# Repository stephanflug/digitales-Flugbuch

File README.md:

<div align="center" width="100%">
    
</div>

# Digitales Flugbuch für Modellflug Vereine

Mit der Software und der Verbindung zu einem Raspberry Pi Zero kann eine digitale Aufzeichnung erstellt werden, die den Anforderungen der aktuellen Verordnung (EU) 2019/947 entspricht.Für Österreich und Deutschland(kann man unter Einstellungen festlegen)

## Kontakt  
Bei Fragen können Sie mich gerne per E-Mail erreichen:  
📧 [steuerung@gmx.at](mailto:steuerung@gmx.at)
oder auch auf dieser Seite [Flugbuch](https://flugbuch.gltdienst.home64.de))

## ⭐ Features

- 🧑‍💼 RFID-Erkennung und Nutzerverifizierung: Wenn ein Benutzer seinen RFID-Chip auf das Lesegerät legt, wird die aktuelle Uhrzeit    zusammen mit dem Namen des Benutzers aus der Benutzerdatei gespeichert. 
- ⌨️ Falls der Benutzer nicht in der Benutzerdatei existiert, wird eine Fehlermeldung ausgegeben.

## ⭐ NEU!

### 🖥️ Flugbuch Cloud Server Panel (Windows) – ab Version 3.9.0

Mit Version **v3.9.0** steht ein neues **Flugbuch Cloud Server Panel für Windows** zur Verfügung.  
Das Panel läuft lokal auf einem Windows-Rechner (z. B. im Vereinsheim) und verbindet sich automatisch mit dem Vereinsflugbuch in der Flugbuch Cloud. Der volle Funktionsumfang des Flugbuchs steht direkt zur Verfügung.

👉 Release-Details:  
https://github.com/stephanflug/digitales-Flugbuch/releases

---

### 🔎 RFID Chip Scanner (Windows & Android)

Zusätzlich zum Flugbuch stehen einfache Hilfstools zum Auslesen der UID von RFID-/NFC-Chips zur Verfügung:

- 🖥️ Windows-Tool für USB-RFID-Lesegeräte  
- 📱 Android-App für NFC-fähige Smartphones  

Die Tools lesen ausschließlich die UID des Chips aus, zeigen sie direkt an und arbeiten vollständig eigenständig.  
Die UID kann im Flugbuch zur eindeutigen Zuordnung von Nutzerchips verwendet werden.

👉 [Zum RFID Chip Scanner](./Tool%20Software/RFID%20Chip%20Scanner/README.md)

---

### 💾 Flugbuch Basic Image

Ein fertiges **Flugbuch Basic Image** steht zum Download bereit.  
Einfach herunterladen und auf die SD-Karte speichern.  
**Bitte unbedingt die Installationsanleitung beachten.**

👉 [Installationsanleitung (PDF)](https://github.com/stephanflug/digitales-Flugbuch/tree/main/Dokumentation/Installation/Flugbuch%20Images)
👉 [Flugbuch Basic Image herunterladen](https://github.com/stephanflug/digitales-Flugbuch/releases)
---

### 📈 Altitude Sensor (ab Version 3.5)

Ab Version **3.5** steht die **Altitude-Sensor-Funktion** zur Verfügung.

👉 [Anleitung (PDF)](https://github.com/stephanflug/digitales-Flugbuch/blob/main/Dokumentation/FlugBuch/RFID%20Flugbuch/Altitude%20Sensor%20beim%20Flugbuch%20einbindenV1.0.pdf)  
👉 Altitude Sensor Projekt: https://github.com/stephanflug/AltitudeSensor

---

### 🧪 Aktuelle getestete Geräte

- ✅ **Pi Zero W2** – getestet  
- ✅ **Pi 3B** – getestet  
- 🔄 **Pi 4** – getestet  
- ⏳ **Pi 5** – getestet

## ⭐ Möglichkeiten:
    -Keinen Cloudzwang
    -Flugbuch-Auswertung direkt auf dem Gerät
    -Möglichkeit, das gesamte Flugbuch zu löschen
    -Flugbuch Einträge bearbeiten
    -Flugbuch-Ausgabe im JSON-Format
    -Flugbuch export in CSV
    -Systeminformationen anzeigen
    -Mail versand
    -Browser Zugang für die Verwaltung
    -Serviceebene direkt auf dem Gerät
    -MQTT
    -MFSD Schnitstelle
    -Kann auch ohne Internet betrieben werden(Nur wenn eine RTC Batterie verbaut wurde)
    -Backup und Restore
    -Viewer Dashboard für eine externen Anzeige via Browser
    -Rest-API Schnitstelle die Flugbuchdaten zu übermitteln
    -Ab der 3.5 Version ist es jetzt möglich einen Altitude Sensor zu verwenden.
    -Bossserver Funktionen.Eine externe Betriebsaufzeichnung auf dem Vereinsserver.
    -VPN Zugang direkt zum Gerät via Flugbuch Cloud Server oder Verein eigenen Server
    -Integration in Areoclub Flugbuch Online

## 🔧 Vorbereitung: 
```
Benötigte Hardware
- ✅ Raspberry Pi 3 oder höher oder Raspberry Pi 2 Zero. Vereine über 30 User sollten einen Pi 4 verwenden.
- ✅ Speicherkarte (microSD) Kapazität: Mindestens 16 GB, idealerweise 32 GB oder mehr.
- ✅ Ein stabiles und ausreichend starkes Netzteil.
- ✅ Ein Gehäuse 
- ✅ Einen Kühlkörper für den Prozessor.
- ✅ RFID-Modul MFRC522
- ✅ 16-Tasten-Keypad (4x4) mit I2c
- ✅ 1602 LCD-Display mit I2C-Modul
- ✅ RFID-Tags oder -Karten
- ✅ RTC Batterie für den offline Modus(nur wenn das Gerät kein Internet hat)
```
## 🚀 Schnellstart

Verwenden Sie das bereits vorbereitete Image – das spart Zeit und schont die Nerven.

👉 [**Installation: Betriebssystem auf SD-Karte**](https://github.com/stephanflug/digitales-Flugbuch/releases)
👉 [**Doko: Betriebssystem auf SD-Karte**](https://github.com/stephanflug/digitales-Flugbuch/blob/main/Dokumentation/Installation/Flugbuch%20Images/Anleitung_Flugbuch_Images.pdf)  

## 🛠️ Alternative Installation auf einem eigenen Raspberry Pi

Wenn Sie das fertige Image nicht verwenden möchten, können Sie die Software auch manuell auf einem selbst eingerichteten Raspberry Pi installieren.

### ✅ Voraussetzungen

- **Hardware:** Raspberry Pi Zero W2 (oder kompatibles Modell)
- **Betriebssystem:** Vorinstalliertes Linux auf der SD-Karte  
  - **Empfohlen:** Raspberry Pi OS Lite oder Raspberry Pi OS Desktop  
  - **Alternativen:** Ubuntu MATE, DietPi, Arch Linux (sofern kompatibel mit Raspberry Pi)
  -  Speichermedium (SD-Karte) Hochwertige SD-Karte (z. B. SanDisk High Endurance oder Samsung Pro Endurance).

### 📦 Vorbereitung

#### 1. Betriebssystem installieren

Falls noch kein Betriebssystem installiert ist:

- Laden Sie den [**Raspberry Pi Imager**](https://www.raspberrypi.com/software/) herunter.
- Wählen Sie ein geeignetes Linux-Betriebssystem (z. B. Raspberry Pi OS).
- Installieren Sie es auf die SD-Karte.

👉 Eine Schritt-für-Schritt-Anleitung finden Sie in der [offiziellen Raspberry Pi-Dokumentation](https://www.raspberrypi.com/documentation/computers/getting-started.html).

#### 2. Raspberry Pi einrichten

- SD-Karte in den Raspberry Pi einlegen
- Monitor, Tastatur und Maus anschließen
- Gerät starten und überprüfen, ob das System korrekt läuft
- Internetverbindung sicherstellen (WLAN oder Ethernet)

> ⚠️ **Hinweis:** Ohne ein vorinstalliertes Linux-Betriebssystem kann dieses Projekt nicht ausgeführt werden. Bitte stellen Sie sicher, dass das System korrekt installiert und betriebsbereit ist, bevor Sie fortfahren.

###
1. Vorbereitungen nur wenn Docker noch nicht auf dem System installiert wurde sonst weiter mit Postion 3
###  
Als Video ansehen:    <a href="https://github.com/stephanflug/digitales-Flugbuch/blob/main/Installation/Neuinstallation/Video/InstallationVideoFlugBuchsoftware.mp4" target="_blank">Video</a>

Aktualisiere das System:
```
sudo apt update
sudo apt upgrade -y
```

Die empfohlene Methode zur Installation von Docker auf einem Raspberry Pi ist die Verwendung des offiziellen Installationsskripts von Docker, das alle notwendigen Repositorys und Schritte berücksichtigt. 
```
curl -fsSL https://get.docker.com -o get-docker.sh
```
```
sudo sh get-docker.sh
```

2. Docker-Dienst aktivieren
```
sudo systemctl start docker
```
```
sudo systemctl enable docker
```
3.Verzeichniss erstellen für script
```
sudo mkdir -p /opt/digitalflugbuch
```
4.Wechsel dann in das Verzeichnis:
```
cd /opt/digitalflugbuch
```

5a. Herunterladen des Skripts mit wget mit Raspberry Pi 3/4/5 Zero 2W oder höher: Prozessor ARMV7
```
sudo wget -O script.sh https://raw.githubusercontent.com/stephanflug/digitales-Flugbuch/main/script_armv7.sh
```

6. Anmeldeung als root Benutzer wenn das Passwort noch nicht gesetzt wurde mit sudo passwd root
```
su
```

6. Script ausführen.
```
sudo bash script.sh
```
7.Raspi-Config aufrufen
```
sudo raspi-config
```
Menüoptionen von raspi-config
> Interface Options
>Aktivierung von Schnittstellen wie  I2C, SPI

8.Gerät neustarten
```
sudo reboot
```

Beispielablauf:
Das Skript wird heruntergeladen und im aktuellen Verzeichnis gespeichert.
Es wird ausführbar gemacht, sodass du es wie ein Programm starten kannst.
Schließlich wird das Skript ausgeführt, und es erledigt alle im Code definierten Aufgaben.

9. Status prüfen:
```
sudo docker ps
```

10. Danach können Sie die Verwaltungsseite öffnen.
```
Startseite url:http://<IPAdresse>:1880/home
```

11 Schaltplan Prinzipschema:   <a href="https://github.com/stephanflug/digitales-Flugbuch/blob/main/Schaltplan/BelegungsaufstellungV1.0.pdf" target="_blank">Belegungsaufstellung</a>

11a Version 1 mit RFID RC522 (alte Version. Empfehlung:Bei Neuinstallation Version 2 zu verwenden)

11b Version 1B mit RFID RC522 + RTC

11c Version 2 mit RFID PN532 + (RTC muss man nicht ausführen wenn das Gerät Internet Zugang hat)

12. Zugriff via Browser: Weitere Bilder Hier: <a href="https://github.com/stephanflug/digitales-Flugbuch/tree/main/Bilder/Webbedienung" target="_blank">Bilder</a>

13. Videos:

###
1.1 Neues Update einspielen

Hinweis: Wenn Sie bereits das fertige Image verwenden, müssen Sie lediglich die IP-Adresse des Geräts in den Browser eingeben. Sie gelangen dann direkt zur Grundkonfiguration, in der Sie im Menü den Punkt „Flugbuch-Update“ finden.
Diese Schritte sind in diesem Fall nicht mehr erforderlich.

1.2 Wechsel in das Verzeichnis:
```
cd /opt/digitalflugbuch
```
1.3 Herunterladen des Skripts
```
sudo wget -O update_script.sh https://raw.githubusercontent.com/stephanflug/digitales-Flugbuch/main/update_script_armv7.sh
```
1.4  Anmeldeung als root Benutzer
```
su
```

1.5. Script ausführen.
```
sudo bash update_script.sh
```
1.6.Gerät neustarten
```
sudo reboot
```

### ☕ Unterstütze das Büro-Kaffeekonto!

Damit der Kaffee im Büro nie ausgeht und die Entwicklung weiter auf Hochtouren läuft, freuen wir uns über eine kleine Unterstützung. ☕💻

Jeder Beitrag hilft dabei, die Kaffeemaschine am Laufen zu halten und sorgt für genügend Energie für neue Ideen, Funktionen und Updates.

**☕ [Kaffee via PayPal spendieren](https://paypal.me/stephanflug)**

Vielen Dank für deine Unterstützung! ❤️

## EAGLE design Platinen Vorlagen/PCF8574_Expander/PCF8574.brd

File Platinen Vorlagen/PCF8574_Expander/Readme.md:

Platinen-Layout ist mit "Eagle 7" gemacht , die e12 Datei im Isolationsfräsen mit "Estlcam 12"

von Manfred Stratmann

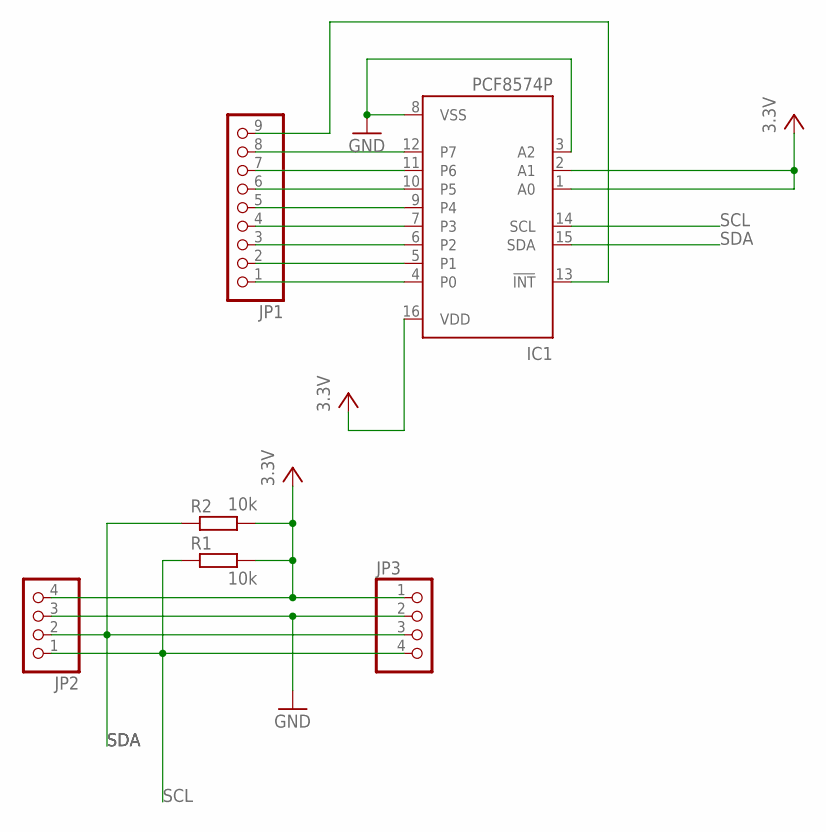
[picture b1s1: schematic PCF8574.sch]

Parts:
IC1: PCF8574P; DIL16
JP1: PINHD-1X9; 1X09
JP2, JP3: PINHD-1X4/90; 1X04/90
R1, R2: 10k; 0309/12

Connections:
GND: IC1.3 (A2), IC1.8 (VSS), JP2.3, JP3.2
unnamed: IC1.4 (P0), JP1.1
unnamed: IC1.5 (P1), JP1.2
unnamed: IC1.6 (P2), JP1.3
unnamed: IC1.7 (P3), JP1.4
unnamed: IC1.9 (P4), JP1.5
unnamed: IC1.10 (P5), JP1.6
unnamed: IC1.11 (P6), JP1.7
unnamed: IC1.12 (P7), JP1.8
unnamed: IC1.13 (!INT), JP1.9
SCL: IC1.14 (SCL), JP2.1, JP3.4, R1.1
SDA: IC1.15 (SDA), JP2.2, JP3.3, R2.1
VCC: IC1.1 (A0), IC1.2 (A1), IC1.16 (VDD), JP2.4, JP3.1, R1.2, R2.2

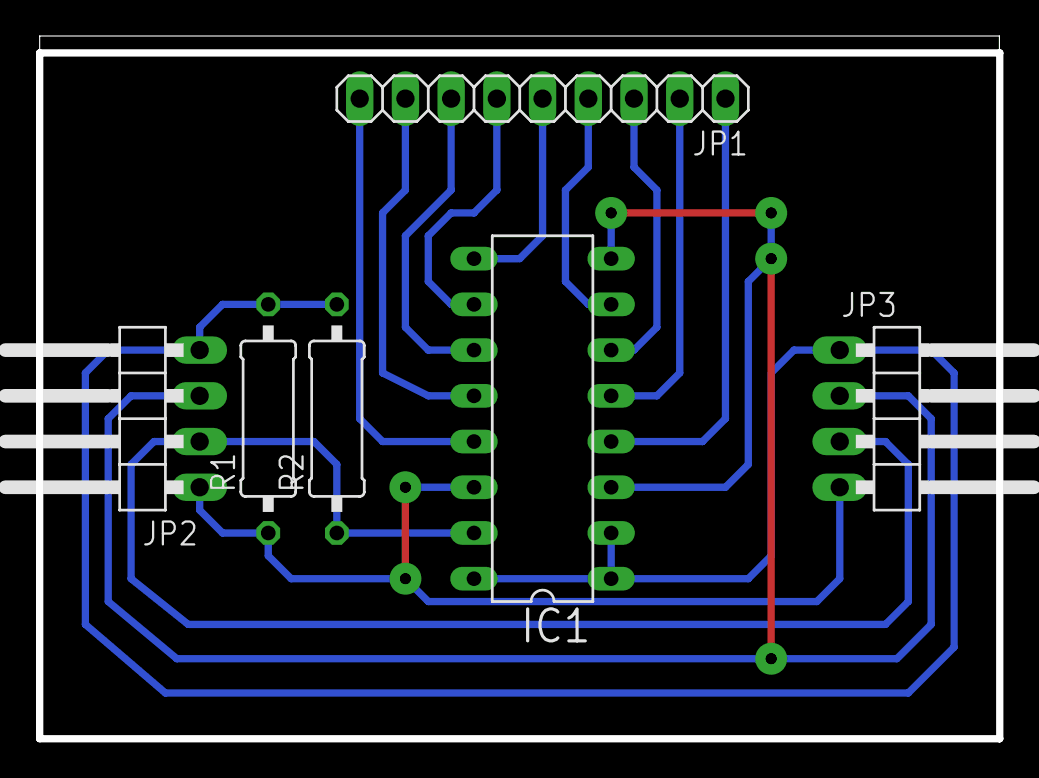
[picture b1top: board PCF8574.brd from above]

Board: 2 copper layers, 53.3 x 38.8 mm, 6 parts (0 on the bottom side), 13 nets.

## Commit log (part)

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2025-05-16 README.md
2025-07-03 update_script_armv7.sh
2025-07-09 WireGuardClient.sh
2025-07-09 readme.json
2025-07-15 uninstall_wireguard.sh
2025-08-02 kioskViewFlugbuch.sh
2025-08-02 KioskViewerFlugbuch.sh
2025-08-03 FlugbuchViewer.sh
2025-08-19 safeBoot.sh
2025-10-15 Pi4_System_Anpassungen.sh
2025-10-15 sdcheck.sh
2025-10-15 testverzeichniss.sh
2025-10-15 healthcheck.sh
2025-10-15 Pi3_System_Anpassungen.sh
2025-10-16 Support_Help.sh
2025-10-18 DNS_repair.sh
2025-10-19 WireGuardClient_BetaTest.sh
2025-10-20 update_script_armv7_testing.sh
2025-10-20 Pi5_System_Anpassungen.sh
2025-11-28 Flugbuch_Cloud.sh
2025-11-28 Flugbuch_Cloud_Server.sh
2025-12-20 LICENSE
2026-02-17 FlugbuchViewer_PI5.sh
2026-02-17 FlugbuchViewer_PI3_PI4.sh
2026-02-24 NodeRed_PI3_PI4_PI5
2026-02-24 NodeRed_PI3_PI4_PI5.sh
2026-04-12 Externe Backup Funktion.sh
2026-04-12 Externe_Backup _Funktion.sh
2026-04-12 Backup_Funktion.sh
